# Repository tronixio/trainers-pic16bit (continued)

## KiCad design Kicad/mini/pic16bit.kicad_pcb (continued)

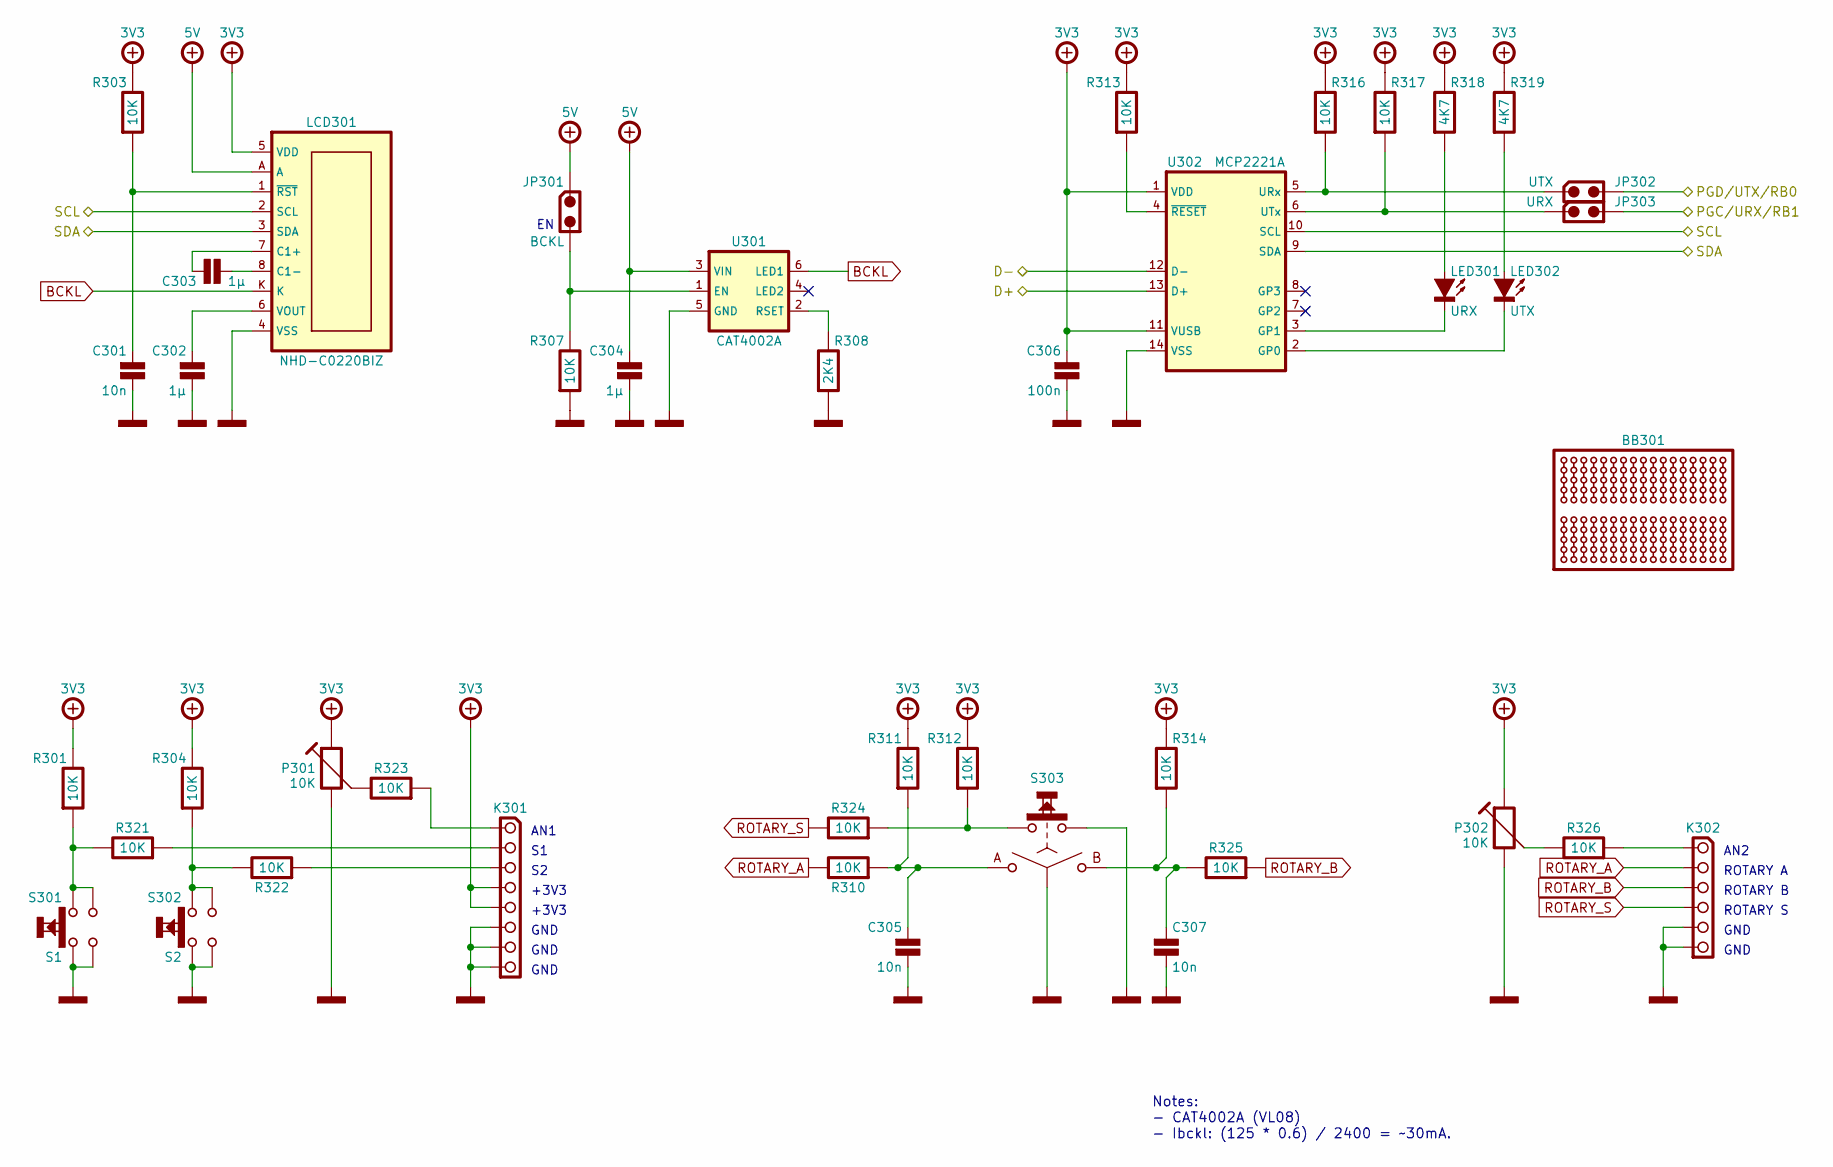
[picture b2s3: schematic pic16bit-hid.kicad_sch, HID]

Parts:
BB301: BREADBOARD-170; Mouser 854-BB170
C301, C305, C307: 10n; CAPACITOR-SMD-1206; Voltage 100V; Tolerance 5%; Mouser 80-C1206C103J1R
C302, C303, C304: 1µ; CAPACITOR-SMD-1206; Voltage 16V; Tolerance 10%; Mouser 80-C1206C105K4R
C306: 100n; CAPACITOR-SMD-1206; Voltage 50V; Tolerance 5%; Mouser 80-C1206C104J5R
JP301: BCKL; HARWIN-M20-999024x; Mouser 855-M20-999024
JP302: UTX; HARWIN-M20-999024x; Mouser 855-M20-999024
JP303: URX; HARWIN-M20-999024x; Mouser 855-M20-999024
K301: HARWIN-254-F-1X08-VERTICAL; HARWIN-M20-782084x; Mouser 855-M20-782084
K302: HARWIN-254-F-1X06-VERTICAL; HARWIN-M20-782064x; Mouser 855-M20-782064
LCD301: NHD-C0220BIZ; Mouser 763-C0220BIZ-FSW-FBW
LED301: URX; LED-SMD-1206; Mouser 604-APT3216LVBCD
LED302: UTX; LED-SMD-1206; Mouser 604-APT3216LVBCD
P301, P302: 10K; PIHER-PT10MV; Tolerance 20%; Mouser 531-PT10MV-10K
R301, R303, R304, R307, R310, R311, R312, R313, R314, R316, R317, R321, R322, R323, R324, R325, R326: 10K; RESISTOR-SMD-1206; Tolerance 5%; Mouser 660-RK73B2BTTDD103J
R308: 2K4; RESISTOR-SMD-1206; Tolerance 5%; Mouser 660-RK73B2BTTDD242J
R318, R319: 4K7; RESISTOR-SMD-1206; Tolerance 5%; Mouser 660-RK73B2BTTDD472J
S301: S1; CK-KSA-TH; Mouser 611-KSA0M911LFT
S302: S2; CK-KSA-TH; Mouser 611-KSA0M911LFT
S303: BOURNS-PEC12R-24DENTS-SWITCH; BOURNS-PEC12R-SWITCH; Mouser 652-PEC12R-4215F-S24
U301: CAT4002A; SC-70-6; Mouser 863-CAT4002ASD-GT3
U302: MCP2221A; SOIC-14; Mouser 579-MCP2221A-I/SL

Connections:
/HID/D+: U302.13 (D+); also elsewhere on the board
/HID/D-: U302.12 (D-); also elsewhere on the board
/HID/SCL: LCD301.2 (SCL), U302.10 (SCL); also elsewhere on the board
/HID/SDA: LCD301.3 (SDA), U302.9 (SDA); also elsewhere on the board
BCKL: LCD301.K, U301.6 (LED1)
unnamed: K301.1, R323.2
unnamed: K301.2, R321.2
unnamed: K301.3, R322.2
unnamed: K302.1, R326.2
unnamed: C303.1, LCD301.7 (C1+)
unnamed: C303.2, LCD301.8 (C1-)
unnamed: C302.1, LCD301.6 (VOUT)
unnamed: C301.1, LCD301.1 (~RST), R303.2
unnamed: LED301.2 (A), R318.2
unnamed: LED301.1 (C), U302.3 (GP1)
unnamed: LED302.2 (A), R319.2
unnamed: LED302.1 (C), U302.2 (GP0)
unnamed: P301.2, R323.1
unnamed: P302.2, R326.1
unnamed: R301.2, R321.1, S301.3, S301.4
unnamed: R304.2, R322.1, S302.3, S302.4
unnamed: R312.2, R324.2, S303.5
unnamed: C305.1, R310.2, R311.2, S303.1 (A)
unnamed: C307.1, R314.2, R325.1, S303.3 (B)
unnamed: JP301.2, R307.1, U301.1 (EN)
unnamed: R308.1, U301.2 (RSET)
unnamed: JP302.1, R316.2, U302.5 (URx)
unnamed: JP303.1, R317.2, U302.6 (UTx)
unnamed: R313.2, U302.4 (~RESET)
PGC/URX/RB1: JP303.2; also elsewhere on the board
PGD/UTX/RB0: JP302.2; also elsewhere on the board
POWER-+3V3: C306.1, K301.4, K301.5, LCD301.5 (VDD), P301.3, P302.3, R301.1, R303.1, R304.1, R311.1, R312.1, R313.1, R314.1, R316.1, R317.1, R318.1, R319.1, U302.1 (VDD), U302.11 (VUSB); also elsewhere on the board
POWER-+5V: C304.1, JP301.1, LCD301.A, U301.3 (VIN); also elsewhere on the board
POWER-GND: C301.2, C302.2, C304.2, C305.2, C306.2, C307.2, K301.6, K301.7, K301.8, K302.5, K302.6, LCD301.4 (VSS), P301.1, P302.1, R307.2, R308.2, S301.1, S301.2, S302.1, S302.2, S303.2 (C), S303.4, U301.5 (GND), U302.14 (VSS); also elsewhere on the board
ROTARY_A: K302.2, R310.1
ROTARY_B: K302.3, R325.2
ROTARY_S: K302.4, R324.1

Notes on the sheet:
AN1
GND
Notes: - CAT4002A (VL08) - Ibckl: (125 * 0.6) / 2400 = ~30mA.
ROTARY A
ROTARY B
AN2
+3V3
ROTARY S

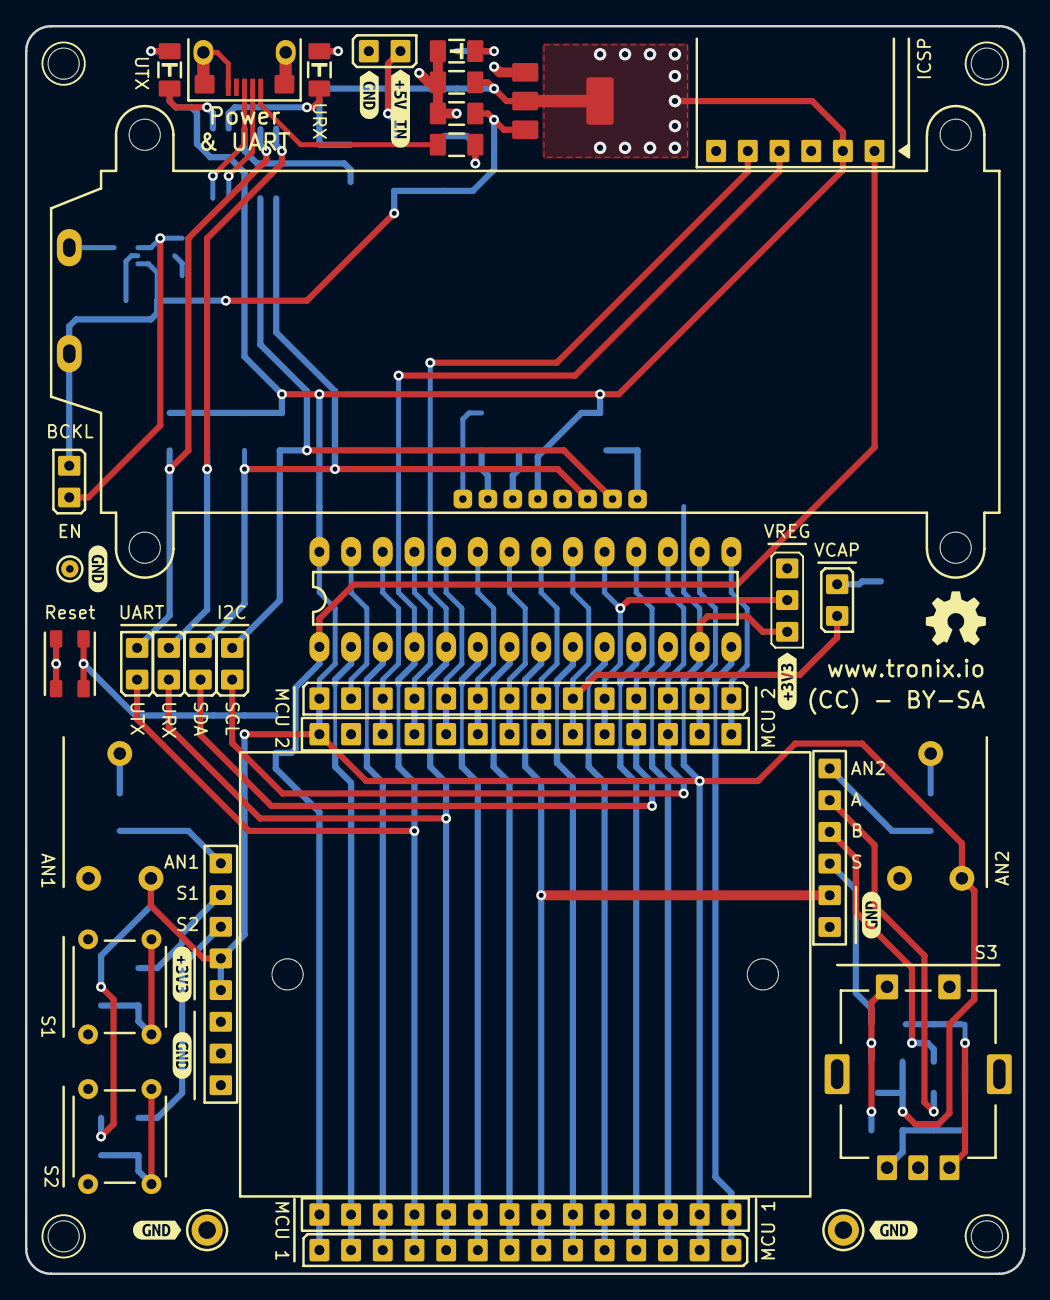
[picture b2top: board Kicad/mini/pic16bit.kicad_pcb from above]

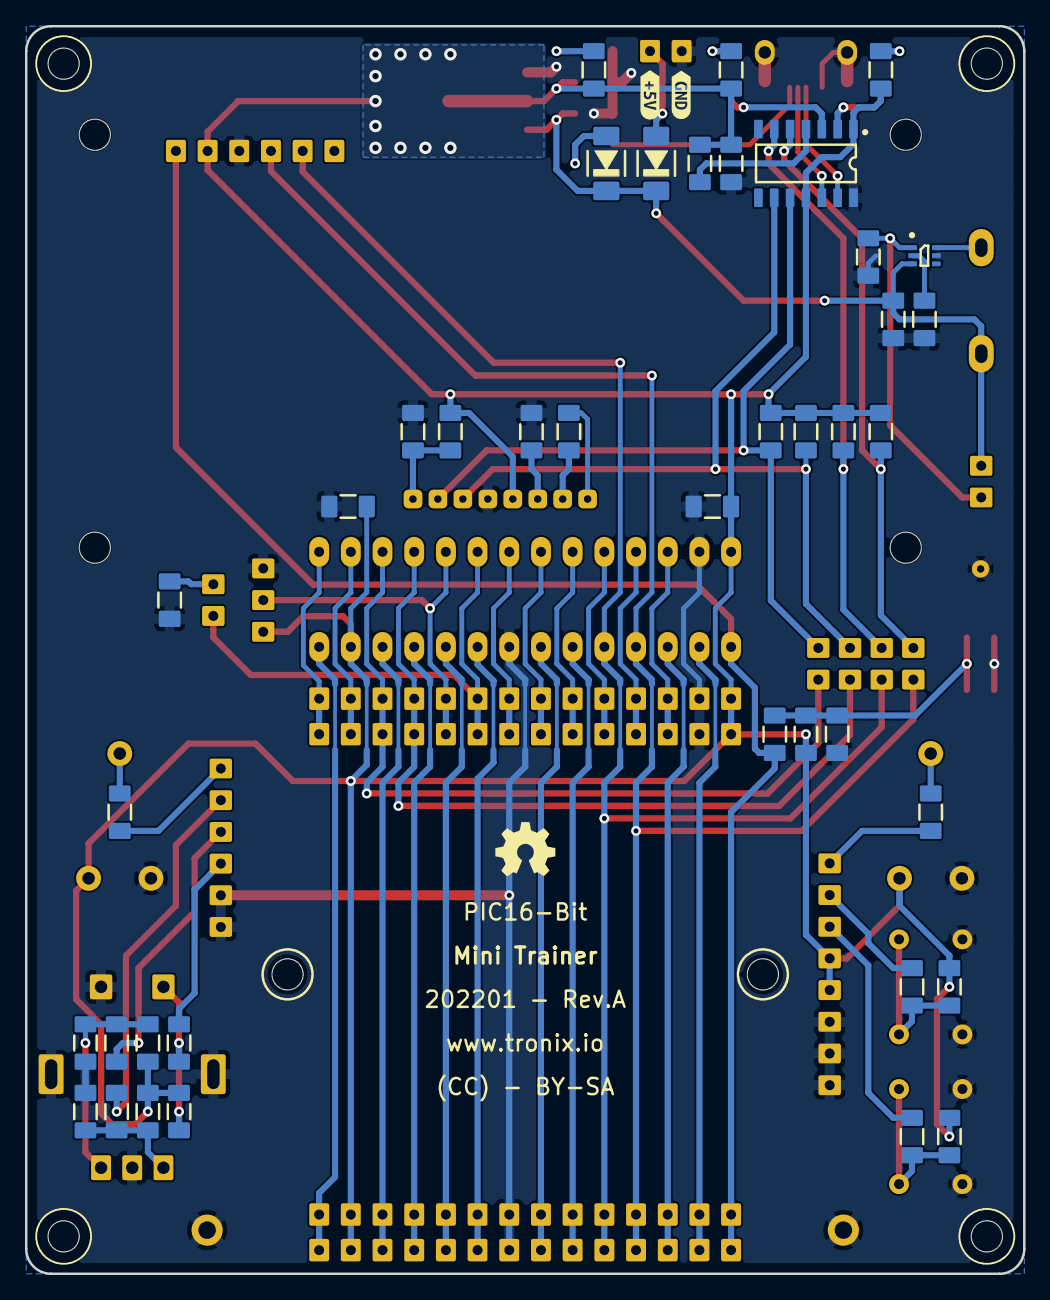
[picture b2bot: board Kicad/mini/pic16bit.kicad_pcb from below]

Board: 2 copper layers, 80.0 x 100.0 mm, 98 parts (42 on the bottom side), 65 nets.

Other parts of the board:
kibuzzard-65F5FF8A: G***; kibuzzard-65F5FF8A
kibuzzard-65F5FF96: G***; kibuzzard-65F5FF96
kibuzzard-65F5FFA5: G***; kibuzzard-65F5FFA5
kibuzzard-65F5FFB1: G***; kibuzzard-65F5FFB1
kibuzzard-65F5FFC7: G***; kibuzzard-65F5FFC7
kibuzzard-65F5FFD5: G***; kibuzzard-65F5FFD5
kibuzzard-65F5FFE7: G***; kibuzzard-65F5FFE7
kibuzzard-65F5FFF2: G***; kibuzzard-65F5FFF2
kibuzzard-65F6000E: G***; kibuzzard-65F6000E
kibuzzard-65F60000: G***; kibuzzard-65F60000
kibuzzard-65F60022: G***; kibuzzard-65F60022

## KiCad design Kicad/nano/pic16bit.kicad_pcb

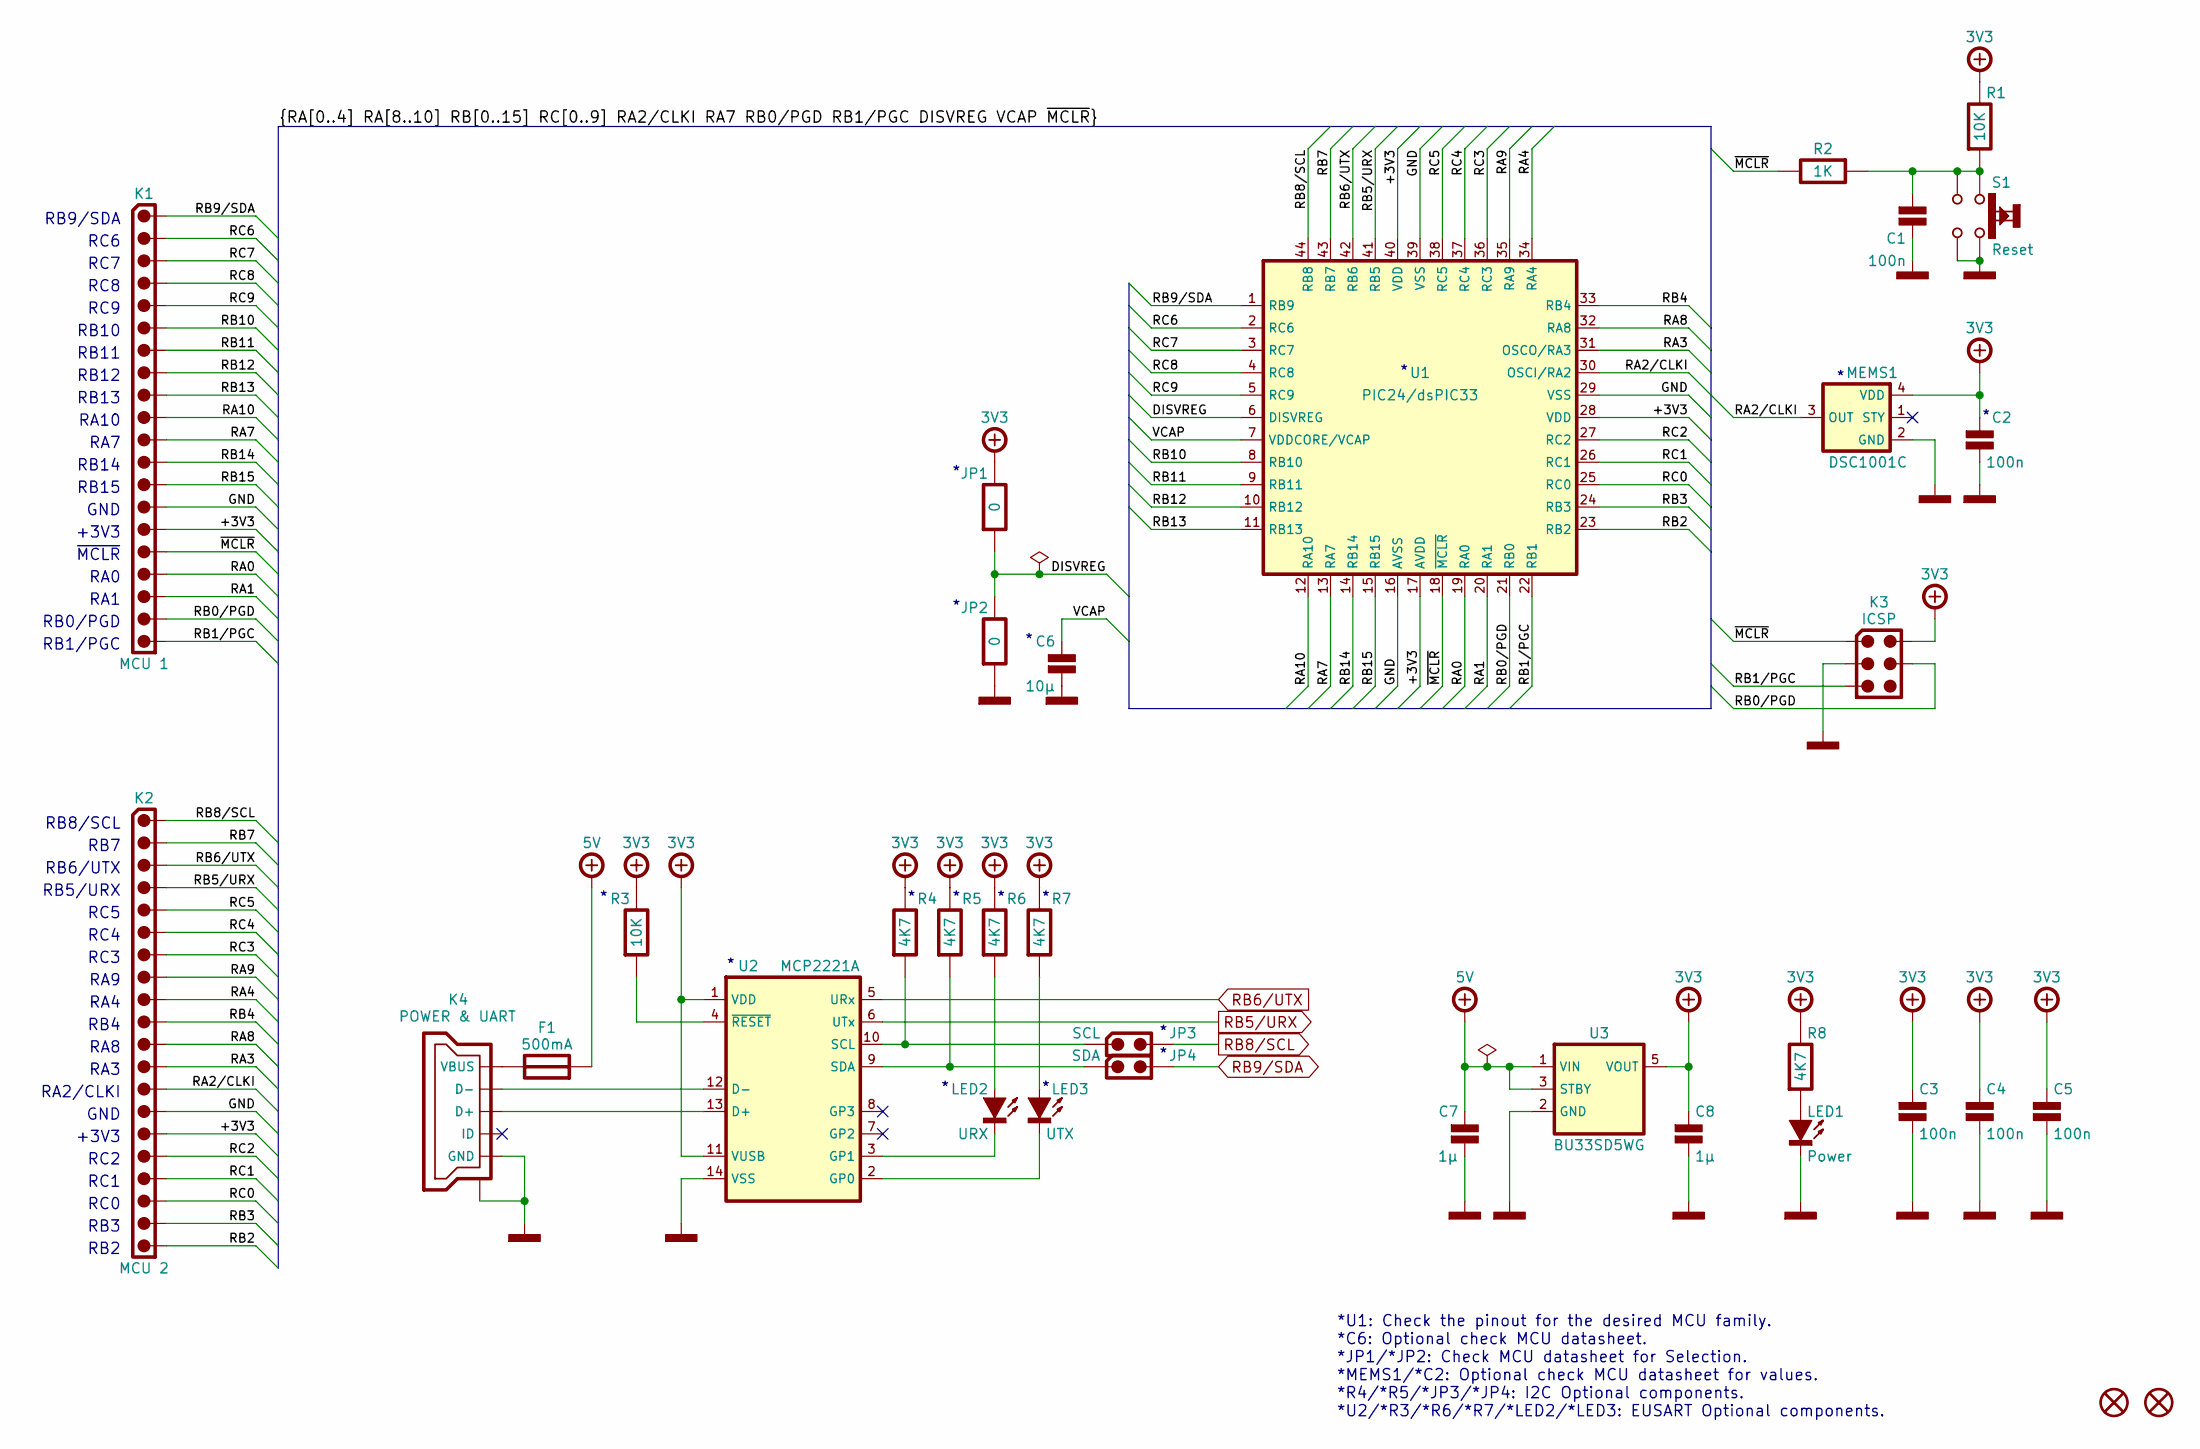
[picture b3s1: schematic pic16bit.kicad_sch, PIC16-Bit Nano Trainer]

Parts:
C1, C2, C3, C4, C5: 100n; CAPACITOR-SMD-0805; Voltage 50V; Tolerance 5%; Mouser 80-C0805C104J5
C6: 10µ; CAPACITOR-SMD-0805; Voltage 25V; Tolerance 10%; Mouser 81-GRM21BZ71E106
C7, C8: 1µ; CAPACITOR-SMD-0805; Voltage 50V; Tolerance 10%; Mouser 187-CL21B105KBFNNNE
F1: 500mA; FUSE-SMD-0805; Mouser 652-MF-PSMF050X-2
H1, H2: HARWIN-JUMPER-0200-03MM-BLACK; HARWIN-M22-190-19X; Mouser 855-M22-19000
JP1, JP2: 0; RESISTOR-SMD-0805; Mouser 660-RK73Z2ATTD
JP3: SCL; HARWIN-M22-25102xx; Mouser 855-M22-25102
JP4: SDA; HARWIN-M22-25102xx; Mouser 855-M22-25102
K1: MCU 1; SAMTEC-TSW-120-22-T-S; Mouser 200-TSW12022TS
K2: MCU 2; SAMTEC-TSW-120-22-T-S; Mouser 200-TSW12022TS
K3: ICSP; HARWIN-M20-998034x; Mouser 855-M20-998034
K4: POWER & UART; USB-TYPE-B-MICRO-TH; Mouser 649-10118193-0001LF
LED1: Power; LED-SMD-0805; Mouser 604-APT2012LVBCD
LED2: URX; LED-SMD-0805; Mouser 604-APT2012LVBCD
LED3: UTX; LED-SMD-0805; Mouser 604-APT2012LVBCD
MEMS1: DSC1001C; CDFN-3225; Mouser 998-1001CI2-024.5760
R1, R3: 10K; RESISTOR-SMD-0805; Tolerance 5%; Mouser 660-RK73B2ATTDD103J
R2: 1K; RESISTOR-SMD-0805; Tolerance 5%; Mouser 660-RK73B2ATTDD102J
R4, R5, R6, R7, R8: 4K7; RESISTOR-SMD-0805; Tolerance 5%; Mouser 660-RK73B2ATTDD472J
S1: Reset; ALPS-SKRPAC; Mouser 688-SKRPACE010
U1: PIC24/dsPIC33; TQFP-44; Mouser 579-FJ64GA104-I/PT
U2: MCP2221A; TSSOP-14; Mouser 579-MCP2221A-I/ST
U3: BU33SD5WG; SOT-23-5; Mouser 755-BU33SD5WG-TR

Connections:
+3V3: C2.1, C3.1, C4.1, C5.1, C8.1, JP1.1, K1.15, K2.15, K3.2 (VCC), MEMS1.4 (VDD), R1.1, R3.1, R4.1, R5.1, R6.1, R7.1, R8.1, U1.17 (AVDD), U1.28 (VDD), U1.40 (VDD), U2.1 (VDD), U2.11 (VUSB), U3.5 (VOUT)
/DISVREG: JP1.2, JP2.1, U1.6 (DISVREG)
/RA0: K1.17, U1.19 (RA0)
/RA1: K1.18, U1.20 (RA1)
/RA2/CLKI: K2.13, MEMS1.3 (OUT), U1.30 (OSCI/RA2)
/RA3: K2.12, U1.31 (OSCO/RA3)
/RA4: K2.9, U1.34 (RA4)
/RA7: K1.11, U1.13 (RA7)
/RA8: K2.11, U1.32 (RA8)
/RA9: K2.8, U1.35 (RA9)
/RA10: K1.10, U1.12 (RA10)
/RB0/PGD: K1.19, K3.4 (ICSPDAT), U1.21 (RB0)
/RB1/PGC: K1.20, K3.5 (ICSPCLK), U1.22 (RB1)
/RB2: K2.20, U1.23 (RB2)
/RB3: K2.19, U1.24 (RB3)
/RB4: K2.10, U1.33 (RB4)
/RB7: K2.2, U1.43 (RB7)
/RB10: K1.6, U1.8 (RB10)
/RB11: K1.7, U1.9 (RB11)
/RB12: K1.8, U1.10 (RB12)
/RB13: K1.9, U1.11 (RB13)
/RB14: K1.12, U1.14 (RB14)
/RB15: K1.13, U1.15 (RB15)
/RC0: K2.18, U1.25 (RC0)
/RC1: K2.17, U1.26 (RC1)
/RC2: K2.16, U1.27 (RC2)
/RC3: K2.7, U1.36 (RC3)
/RC4: K2.6, U1.37 (RC4)
/RC5: K2.5, U1.38 (RC5)
/RC6: K1.2, U1.2 (RC6)
/RC7: K1.3, U1.3 (RC7)
/RC8: K1.4, U1.4 (RC8)
/RC9: K1.5, U1.5 (RC9)
/VCAP: C6.1, U1.7 (VDDCORE/VCAP)
/~MCLR: K1.16, K3.1 (~MCLR), R2.1, U1.18 (~MCLR)
GND: C1.2, C2.2, C3.2, C4.2, C5.2, C6.2, C7.2, C8.2, JP2.2, K1.14, K2.14, K3.3 (GND), K4.5 (GND), K4.SH (SHIELD), LED1.1 (C), MEMS1.2 (GND), S1.3, S1.4, U1.16 (AVSS), U1.29 (VSS), U1.39 (VSS), U2.14 (VSS), U3.2 (GND)
unnamed: C1.1, R1.2, R2.2, S1.1, S1.2
unnamed: K4.3 (D+), U2.13 (D+)
unnamed: K4.2 (D-), U2.12 (D-)
unnamed: F1.1, K4.1 (VBUS)
unnamed: LED1.2 (A), R8.2
unnamed: LED2.2 (A), R6.2
unnamed: LED2.1 (C), U2.3 (GP1)
unnamed: LED3.2 (A), R7.2
unnamed: LED3.1 (C), U2.2 (GP0)
unnamed: JP3.1, R4.2, U2.10 (SCL)
unnamed: JP4.1, R5.2, U2.9 (SDA)
unnamed: R3.2, U2.4 (~RESET)
POWER-+5V: C7.1, F1.2, U3.1 (VIN), U3.3 (STBY)
RB5/URX: K2.4, U1.41 (RB5), U2.6 (UTx)
RB6/UTX: K2.3, U1.42 (RB6), U2.5 (URx)
RB8/SCL: JP3.2, K2.1, U1.44 (RB8)
RB9/SDA: JP4.2, K1.1, U1.1 (RB9)

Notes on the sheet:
RC9
RA2/CLKI
RB12
RC7
RB8/SCL
GND
RB14
RB2
RB13
RC0
RA9
~{MCLR}
RA10
RB11
RC1
RB15
RA3
RC4
RB5/URX
RC8
RB10
RA7
RB1/PGC
*U1: Check the pinout for the desired MCU family. *C6: Optional check MCU datasheet. *JP1/*JP2: Check MCU datasheet for Selection. *MEMS1/*C2: Optional check MCU datasheet for values. *R4/*R5/*JP3/*JP4: I2C Optional components. *U2/*R3/*R6/*R7/*LED2/*LED3: EUSART Optional components.
RC2
RA1
+3V3
RB0/PGD
RB7
RA8
RB6/UTX
RA0
RB3
RC5
RC3
RA4
RB9/SDA
RB4
RC6

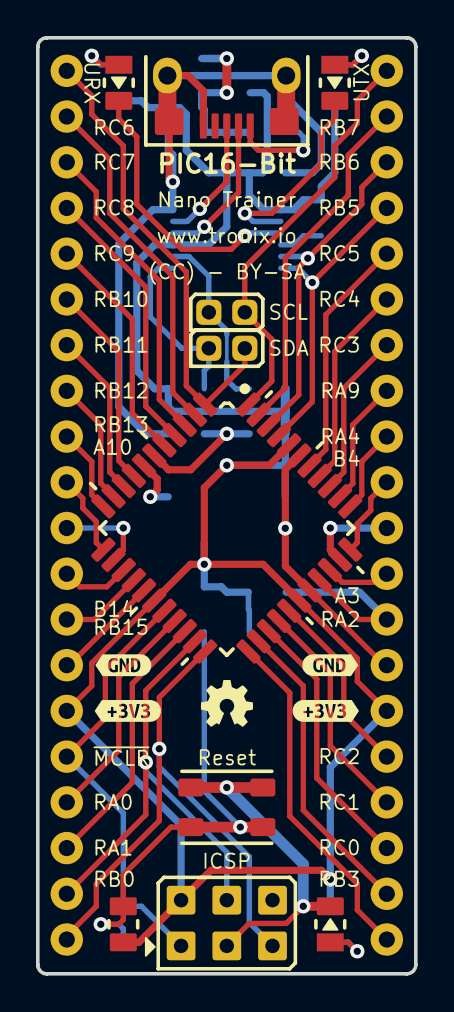
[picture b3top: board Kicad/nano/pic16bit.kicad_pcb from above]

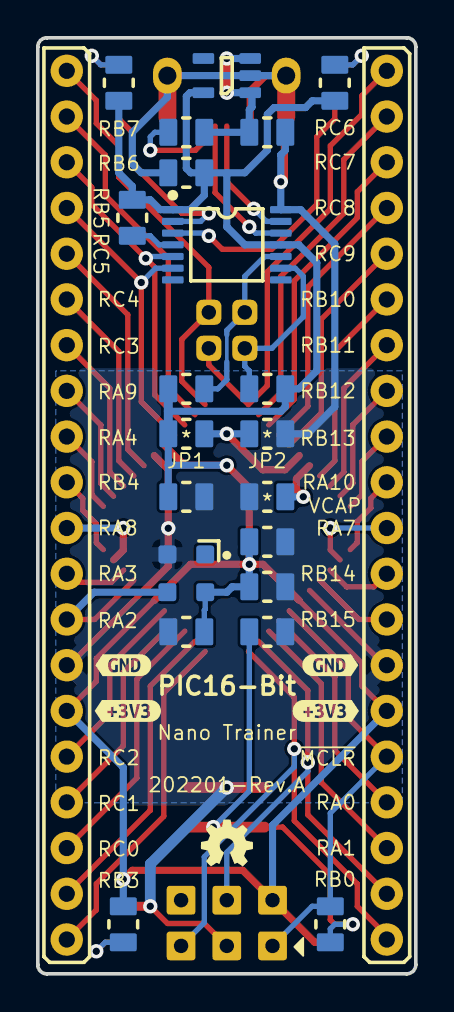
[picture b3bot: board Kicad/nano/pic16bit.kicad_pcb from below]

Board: 2 copper layers, 21.0 x 52.0 mm, 45 parts (28 on the bottom side), 53 nets.

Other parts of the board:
GB: LOGO; OSHW-3MM
GT: LOGO; OSHW-3MM
kibuzzard-65F5C12D: G***; kibuzzard-65F5C12D
kibuzzard-65F5C13A: G***; kibuzzard-65F5C13A
kibuzzard-65F5C14D: G***; kibuzzard-65F5C14D
kibuzzard-65F5C15C: G***; kibuzzard-65F5C15C
kibuzzard-65F5C114: G***; kibuzzard-65F5C114
kibuzzard-65F5C121: G***; kibuzzard-65F5C121
kibuzzard-65F5C168: G***; kibuzzard-65F5C168
kibuzzard-65F5C174: G***; kibuzzard-65F5C174

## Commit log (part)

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2022-01-10 Add Kicad
2022-01-10 Add Features
2022-03-21 Create Mini
2022-03-21 Update Mini
2022-04-01 Update Nano
2022-04-18 Update PIC24FJxxGA10x
2022-04-18 Update Kicad
2022-04-18 Udapte
2022-06-11 Updaet
2022-09-03 PIC16Bit Trainer
2023-01-21 Update Trainer
2024-03-16 Update Nano Kicad 8
2024-03-16 Update Mini Kicad 8
2024-03-17 Update Trainer Kicad 8
2026-04-24 Mini
